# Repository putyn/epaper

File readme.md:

# epaper 
Adventure with epaper panel to create an epaper wifi connected photoframe.

Project is heavly based on [epdiy project](https://github.com/vroland/epdiy) but with a slightly different hardware, [epaper-breakout](epaper-breakout) is the first iteration of the project which will, hopefully, drive an ED060XC3 panel.

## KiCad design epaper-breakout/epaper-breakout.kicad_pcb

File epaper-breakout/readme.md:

`Project status: Work in progress`

## ink-frame rev 0.1

Breakout board for [TPS65185](https://www.ti.com/lit/ds/symlink/tps65185.pdf) which supplies the 5 voltages needed to drive e-ink panels, [BQ24075](https://www.ti.com/lit/ds/symlink/bq24075.pdf) 
battery charger and FPC connector for e-ink panel, should fit ED060XC3 panel.

## pcb render

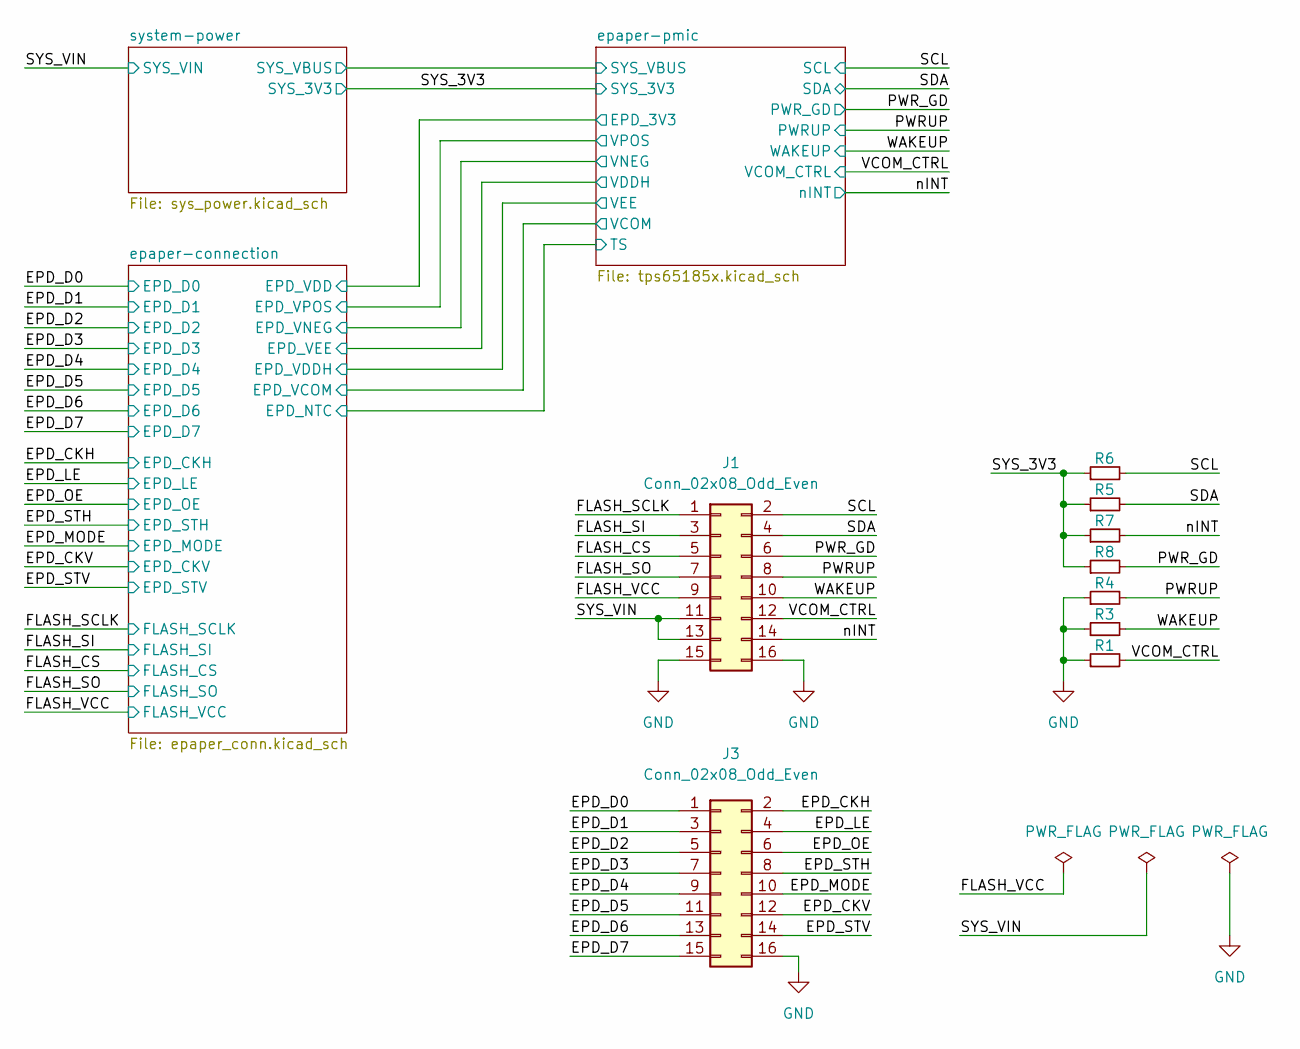
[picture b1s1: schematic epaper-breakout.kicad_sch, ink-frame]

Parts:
J1, J3: Conn_02x08_Odd_Even; PinHeader_2x08_P2.54mm_Vertical
R1, R3, R4, R7, R8: 100k; R_0603_1608Metric; LCSC C25803
R5, R6: 2k2; R_0603_1608Metric; LCSC C4190

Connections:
/EPD_CKH: J3.2; also elsewhere on the board
/EPD_CKV: J3.12; also elsewhere on the board
/EPD_D0: J3.1; also elsewhere on the board
/EPD_D1: J3.3; also elsewhere on the board
/EPD_D2: J3.5; also elsewhere on the board
/EPD_D3: J3.7; also elsewhere on the board
/EPD_D4: J3.9; also elsewhere on the board
/EPD_D5: J3.11; also elsewhere on the board
/EPD_D6: J3.13; also elsewhere on the board
/EPD_D7: J3.15; also elsewhere on the board
/EPD_LE: J3.4; also elsewhere on the board
/EPD_MODE: J3.10; also elsewhere on the board
/EPD_OE: J3.6; also elsewhere on the board
/EPD_STH: J3.8; also elsewhere on the board
/EPD_STV: J3.14; also elsewhere on the board
/FLASH_CS: J1.5; also elsewhere on the board
/FLASH_SCLK: J1.1; also elsewhere on the board
/FLASH_SI: J1.3; also elsewhere on the board
/FLASH_SO: J1.7; also elsewhere on the board
/FLASH_VCC: J1.9; also elsewhere on the board
/PWRUP: J1.8, R4.2; also elsewhere on the board
/PWR_GD: J1.6, R8.2; also elsewhere on the board
/SCL: J1.2, R6.2; also elsewhere on the board
/SDA: J1.4, R5.2; also elsewhere on the board
/SYS_3V3: R5.1, R6.1, R7.1, R8.1; also elsewhere on the board
/SYS_VIN: J1.11, J1.13; also elsewhere on the board
/VCOM_CTRL: J1.12, R1.2; also elsewhere on the board
/WAKEUP: J1.10, R3.2; also elsewhere on the board
/nINT: J1.14, R7.2; also elsewhere on the board
GND: J1.15, J1.16, J3.16, R1.1, R3.1, R4.1; also elsewhere on the board

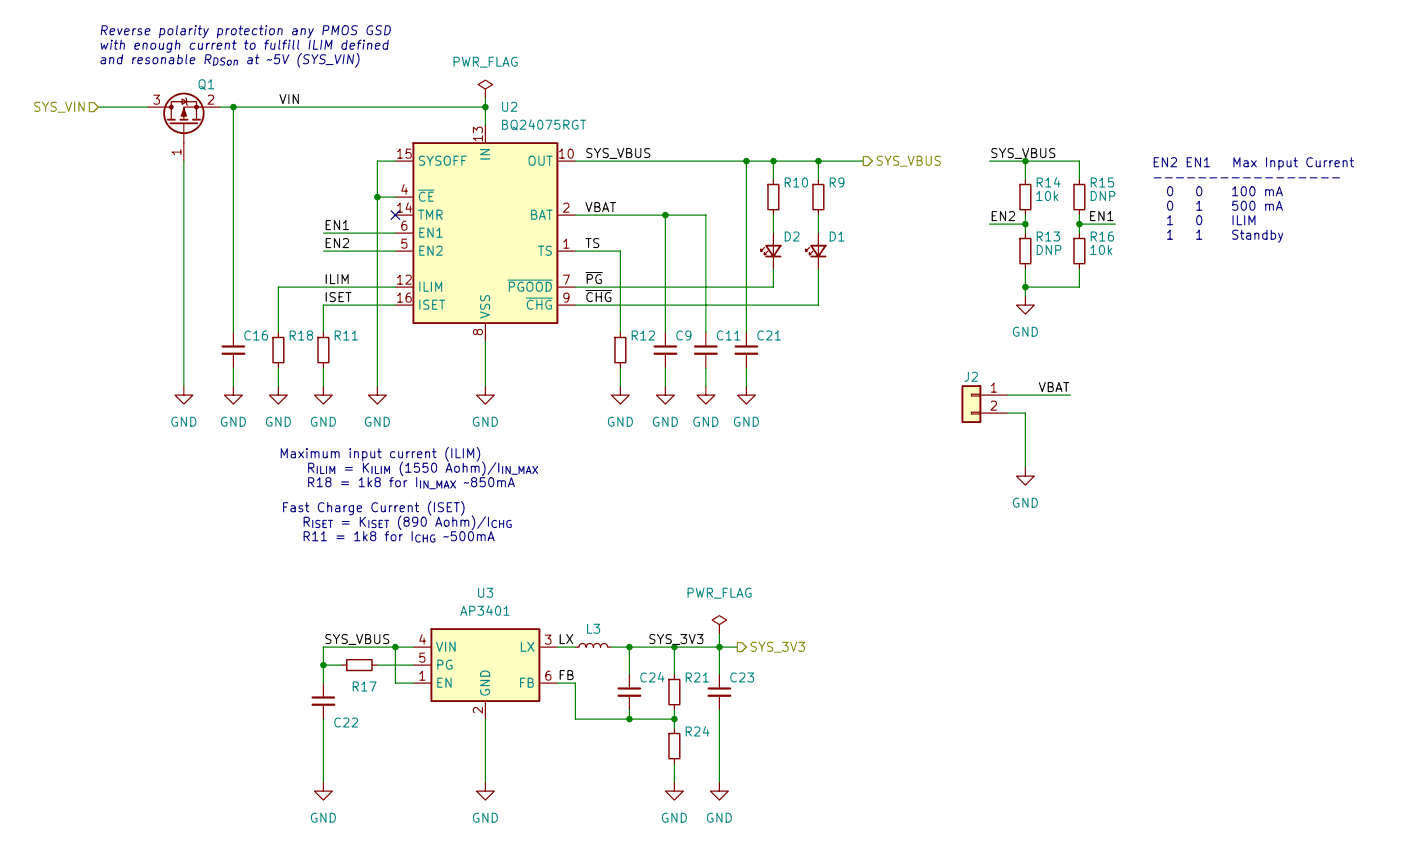
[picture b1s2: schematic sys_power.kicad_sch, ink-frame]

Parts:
C9, C16, C21, C22, C23: 10u;16V; C_0805_2012Metric; LCSC C17024
C11: 100n;25V; C_0603_1608Metric; LCSC C14663
C24: 22p; C_0603_1608Metric; LCSC C1653
D1, D2: RED; LED_0603_1608Metric; LCSC C965800
J2: Conn_01x02; JST_PH_S2B-PH-SM4-TB_1x02-1MP_P2.00mm_Horizontal; LCSC C47647
L3: 2u2; L_Taiyo-Yuden_NR-40xx; LCSC C98027
Q1: AO3401A; SOT-23; LCSC C15127
R9, R10: 2k2; R_0603_1608Metric; LCSC C4190
R11, R18: 1k8; R_0603_1608Metric; LCSC C4177
R12, R14, R16: 10k; R_0603_1608Metric; LCSC C25804
R13, R15: DNP; R_0603_1608Metric
R17, R24: 100k; R_0603_1608Metric; LCSC C25803
R21: 430k; R_0603_1608Metric; LCSC C25969
U2: BQ24075RGT; VQFN-16-1EP_3x3mm_P0.5mm_EP1.45x1.45mm_ThermalVias
U3: AP3401; TSOT-23-6

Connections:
/SYS_3V3: C23.1, C24.1, L3.2, R21.1; also elsewhere on the board
/SYS_VIN: Q1.3 (D); also elsewhere on the board
/epaper-pmic/SYS_VBUS: C21.1, C22.1, R9.1, R10.1, R14.1, R15.1, R17.1, U2.10 (OUT), U2.11 (OUT), U3.1 (EN), U3.4 (VIN); also elsewhere on the board
/system-power/EN1: R15.2, R16.1, U2.6 (EN1)
/system-power/EN2: R13.1, R14.2, U2.5 (EN2)
/system-power/FB: C24.2, R21.2, R24.1, U3.6 (FB)
/system-power/ILIM: R18.1, U2.12 (ILIM)
/system-power/ISET: R11.1, U2.16 (ISET)
/system-power/LX: L3.1, U3.3 (LX)
/system-power/TS: R12.1, U2.1 (TS)
/system-power/VBAT: C9.1, C11.1, J2.1, U2.2 (BAT), U2.3 (BAT)
/system-power/VIN: C16.1, Q1.2 (S), U2.13 (IN)
/system-power/~CHG: D1.1 (K), U2.9 (~CHG)
/system-power/~PG: D2.1 (K), U2.7 (~PGOOD)
GND: C9.2, C11.2, C16.2, C21.2, C22.2, C23.2, J2.2, Q1.1 (G), R11.2, R12.2, R13.2, R16.2, R18.2, R24.2, U2.4 (~CE), U2.8 (VSS), U2.15 (SYSOFF), U2.17 (VSS), U3.2 (GND); also elsewhere on the board
unnamed: D1.2 (A), R9.2
unnamed: D2.2 (A), R10.2
unnamed: R17.2, U3.5 (PG)

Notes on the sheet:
Maximum input current (ILIM) R_{ILIM} = K_{ILIM} (1550 Aohm)/I_{IN_MAX} R18 = 1k8 for I_{IN_MAX} ~850mA
Fast Charge Current (ISET) R_{ISET} = K_{ISET} (890 Aohm)/I_{CHG} R11 = 1k8 for I_{CHG} ~500mA
EN2 EN1 Max Input Current ----------------- 0 0 100 mA 0 1 500 mA 1 0 ILIM 1 1 Standby
Reverse polarity protection any PMOS GSD with enough current to fulfill ILIM defined and resonable R_{DSon} at ~5V (SYS_VIN)

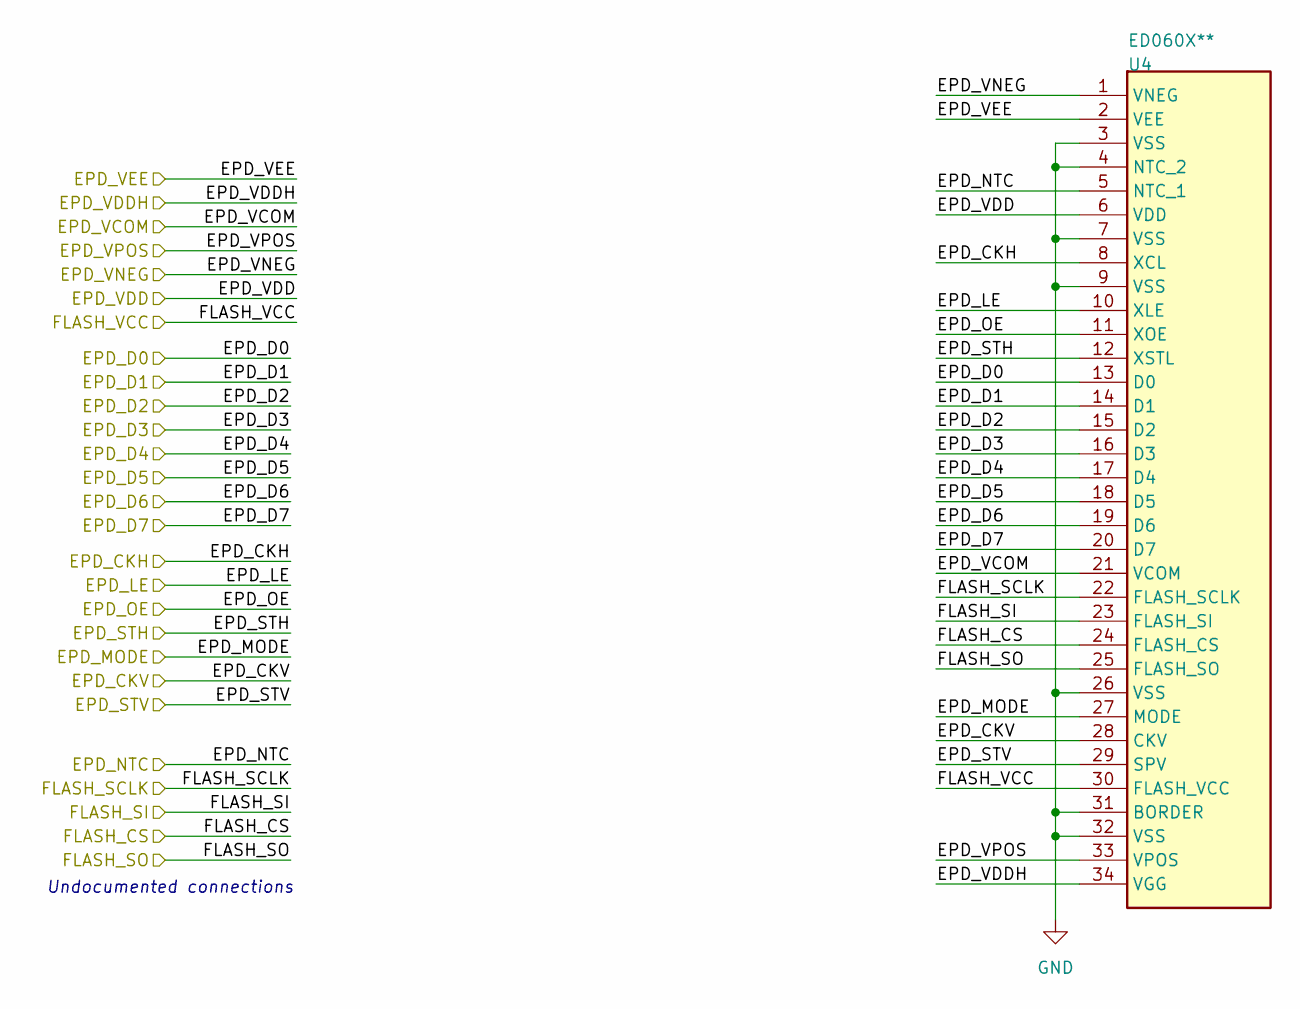
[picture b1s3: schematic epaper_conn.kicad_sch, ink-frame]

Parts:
U4: ED060X**; THD_THD0515-34CL-SN; LCSC C283154

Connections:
/EPD_CKH: U4.8 (XCL); also elsewhere on the board
/EPD_CKV: U4.28 (CKV); also elsewhere on the board
/EPD_D0: U4.13 (D0); also elsewhere on the board
/EPD_D1: U4.14 (D1); also elsewhere on the board
/EPD_D2: U4.15 (D2); also elsewhere on the board
/EPD_D3: U4.16 (D3); also elsewhere on the board
/EPD_D4: U4.17 (D4); also elsewhere on the board
/EPD_D5: U4.18 (D5); also elsewhere on the board
/EPD_D6: U4.19 (D6); also elsewhere on the board
/EPD_D7: U4.20 (D7); also elsewhere on the board
/EPD_LE: U4.10 (XLE); also elsewhere on the board
/EPD_MODE: U4.27 (MODE); also elsewhere on the board
/EPD_OE: U4.11 (XOE); also elsewhere on the board
/EPD_STH: U4.12 (XSTL); also elsewhere on the board
/EPD_STV: U4.29 (SPV); also elsewhere on the board
/FLASH_CS: U4.24 (FLASH_CS); also elsewhere on the board
/FLASH_SCLK: U4.22 (FLASH_SCLK); also elsewhere on the board
/FLASH_SI: U4.23 (FLASH_SI); also elsewhere on the board
/FLASH_SO: U4.25 (FLASH_SO); also elsewhere on the board
/FLASH_VCC: U4.30 (FLASH_VCC); also elsewhere on the board
/epaper-connection/EPD_NTC: U4.5 (NTC_1); also elsewhere on the board
/epaper-connection/EPD_VCOM: U4.21 (VCOM); also elsewhere on the board
/epaper-connection/EPD_VDD: U4.6 (VDD); also elsewhere on the board
/epaper-connection/EPD_VDDH: U4.34 (VGG); also elsewhere on the board
/epaper-connection/EPD_VEE: U4.2 (VEE); also elsewhere on the board
/epaper-connection/EPD_VNEG: U4.1 (VNEG); also elsewhere on the board
/epaper-connection/EPD_VPOS: U4.33 (VPOS); also elsewhere on the board
GND: U4.3 (VSS), U4.4 (NTC_2), U4.7 (VSS), U4.9 (VSS), U4.26 (VSS), U4.31 (BORDER), U4.32 (VSS); also elsewhere on the board

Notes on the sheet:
Undocumented connections

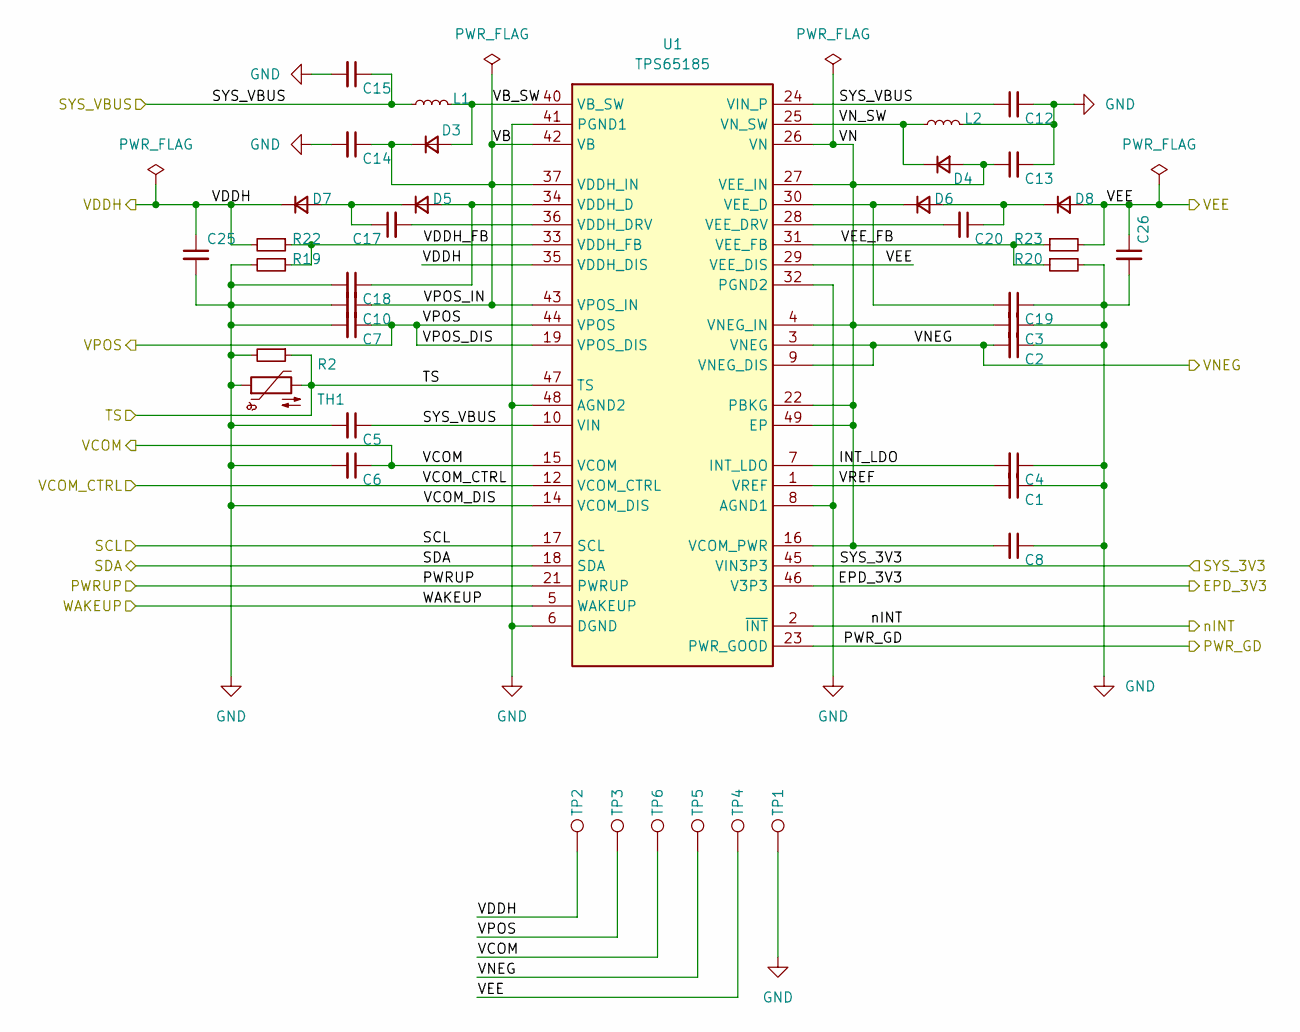
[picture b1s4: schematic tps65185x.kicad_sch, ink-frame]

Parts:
C1, C4, C6: 4u7;6V3; C_0603_1608Metric; LCSC C8032
C2, C3, C7, C8, C10, C13, C14: 4u7;25V; C_0805_2012Metric; LCSC C1779
C5, C12, C15: 10u;16V; C_0805_2012Metric; LCSC C17024
C17, C20: 10n;25V; C_0603_1608Metric; LCSC C1589
C18, C19: 100n;25V; C_0603_1608Metric; LCSC C14663
C25, C26: 4u7;50V; C_0805_2012Metric; LCSC C98192
D3, D4, D5, D6, D7, D8: 1N5819WS; D_SOD-323; LCSC C191023
L1: 2u2; L_Taiyo-Yuden_NR-40xx; LCSC C98027
L2: 4u7; L_Taiyo-Yuden_NR-40xx; LCSC C86081
R2: 43k; R_0603_1608Metric; LCSC C23172
R19: 47k5; R_0603_1608Metric; LCSC C25896
R20: 52k3; R_0603_1608Metric; LCSC C23198
R22, R23: 1M; R_0603_1608Metric; LCSC C22935
TH1: 10k; R_0603_1608Metric; LCSC C13564
TP1, TP2, TP3, TP4, TP5, TP6: TestPoint; TestPoint_Pad_D1.5mm
U1: TPS65185; VQFN-48-1EP_7x7mm_P0.5mm_EP4.1x4.1mm_ThermalVias

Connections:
/PWRUP: U1.21 (PWRUP); also elsewhere on the board
/PWR_GD: U1.23 (PWR_GOOD); also elsewhere on the board
/SCL: U1.17 (SCL); also elsewhere on the board
/SDA: U1.18 (SDA); also elsewhere on the board
/SYS_3V3: U1.45 (VIN3P3); also elsewhere on the board
/VCOM_CTRL: U1.12 (VCOM_CTRL); also elsewhere on the board
/WAKEUP: U1.5 (WAKEUP); also elsewhere on the board
/epaper-connection/EPD_NTC: R2.1, TH1.2, U1.47 (TS); also elsewhere on the board
/epaper-connection/EPD_VCOM: C6.1, TP6.1, U1.15 (VCOM); also elsewhere on the board
/epaper-connection/EPD_VDD: U1.46 (V3P3); also elsewhere on the board
/epaper-connection/EPD_VDDH: C26.1, D8.2 (A), R23.2, TP4.1, U1.29 (VEE_DIS); also elsewhere on the board
/epaper-connection/EPD_VEE: C25.1, D7.1 (K), R22.2, TP2.1, U1.35 (VDDH_DIS); also elsewhere on the board
/epaper-connection/EPD_VNEG: C2.2, TP5.1, U1.3 (VNEG), U1.9 (VNEG_DIS); also elsewhere on the board
/epaper-connection/EPD_VPOS: C7.1, TP3.1, U1.19 (VPOS_DIS), U1.44 (VPOS); also elsewhere on the board
/epaper-pmic/INT_LDO: C4.2, U1.7 (INT_LDO)
/epaper-pmic/SYS_VBUS: C5.1, C12.1, C15.1, L1.1, U1.10 (VIN), U1.24 (VIN_P); also elsewhere on the board
/epaper-pmic/VDDH_FB: R19.1, R22.1, U1.33 (VDDH_FB)
/epaper-pmic/VEE_FB: R20.1, R23.1, U1.31 (VEE_FB)
/epaper-pmic/VN: C3.2, C8.2, C13.1, D4.2 (A), U1.4 (VNEG_IN), U1.16 (VCOM_PWR), U1.22 (PBKG), U1.26 (VN), U1.27 (VEE_IN), U1.49 (EP)
/epaper-pmic/VN_SW: D4.1 (K), L2.2, U1.25 (VN_SW)
/epaper-pmic/VREF: C1.2, U1.1 (VREF)
/nINT: U1.2 (~INT); also elsewhere on the board
GND: C1.1, C2.1, C3.1, C4.1, C5.2, C6.2, C7.2, C8.1, C10.2, C12.2, C13.2, C14.2, C15.2, C18.2, C19.1, C25.2, C26.2, L2.1, R2.2, R19.2, R20.2, TH1.1, TP1.1, U1.6 (DGND), U1.8 (AGND1), U1.14 (VCOM_DIS), U1.32 (PGND2), U1.41 (PGND1), U1.48 (AGND2); also elsewhere on the board
unnamed: C17.1, D5.1 (K), D7.2 (A)
unnamed: C17.2, U1.36 (VDDH_DRV)
unnamed: C18.1, D5.2 (A), U1.34 (VDDH_D)
unnamed 58: C19.2, D6.1 (K), U1.30 (VEE_D); also elsewhere on the board
unnamed 59: C20.1, D6.2 (A), D8.1 (K); also elsewhere on the board
unnamed: C20.2, U1.28 (VEE_DRV)

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
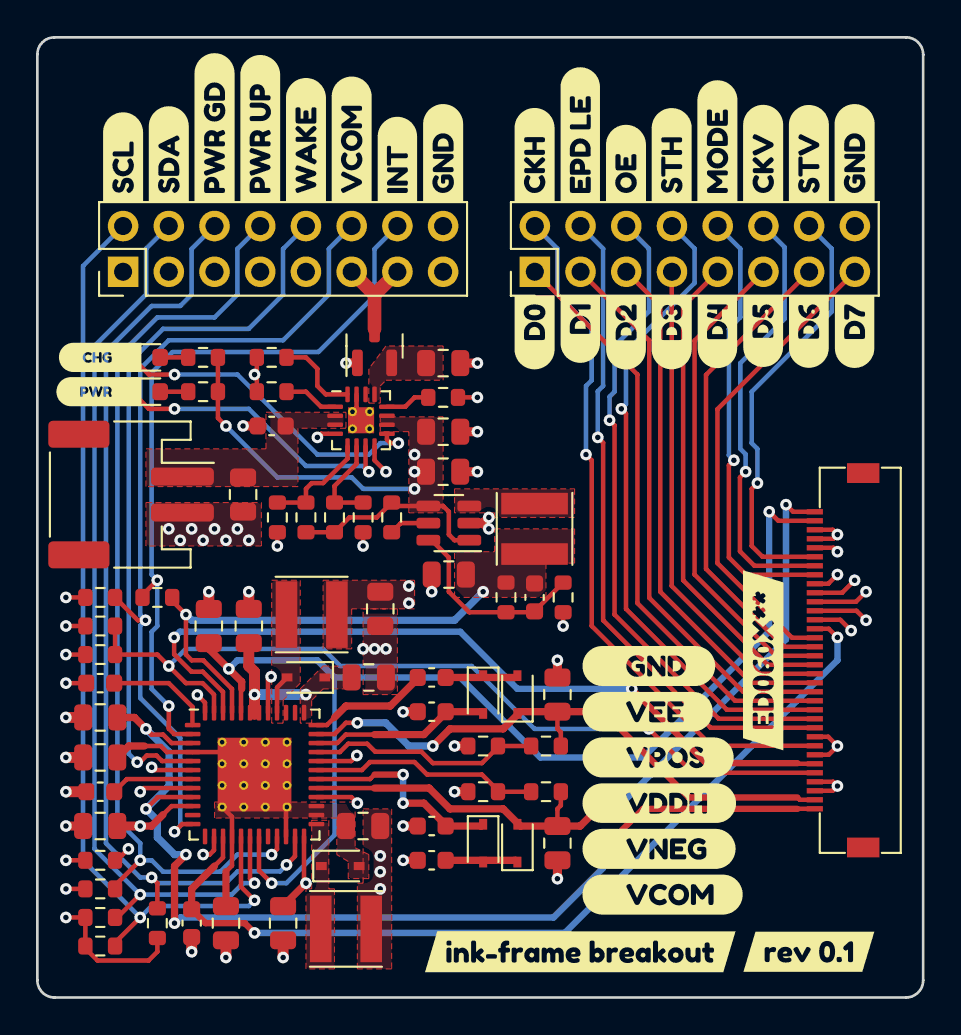
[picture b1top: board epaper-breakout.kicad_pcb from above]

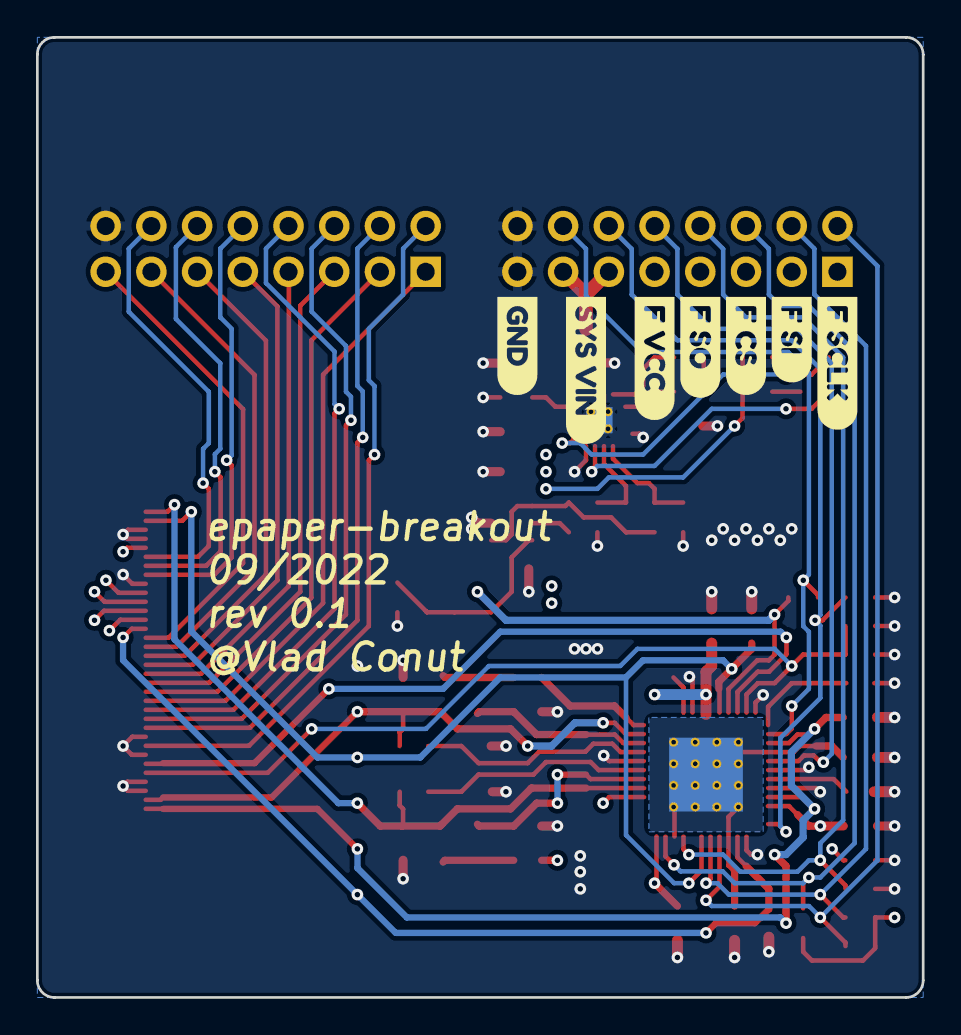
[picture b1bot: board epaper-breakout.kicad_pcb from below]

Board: 4 copper layers, 49.2 x 53.3 mm, 118 parts (7 on the bottom side), 66 nets.

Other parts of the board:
kibuzzard-1: G***; kibuzzard-63060977
kibuzzard-2: G***; kibuzzard-6306091E
kibuzzard-3: G***; kibuzzard-6304CD62
kibuzzard-4: G***; kibuzzard-6304CD58
kibuzzard-5: G***; kibuzzard-6304CD7C
kibuzzard-6: G***; kibuzzard-6304CD98
kibuzzard-7: G***; kibuzzard-6304CDA2
kibuzzard-8: G***; kibuzzard-6304CE57
kibuzzard-9: G***; kibuzzard-6304CE9C
kibuzzard-10, kibuzzard-34, kibuzzard-34#2: G***; kibuzzard-6304CEA6
kibuzzard-11: G***; kibuzzard-6304CAAC
kibuzzard-12: G***; kibuzzard-6304CBD9
kibuzzard-13: G***; kibuzzard-6304CA26
kibuzzard-14: G***; kibuzzard-6304CBCE
kibuzzard-15: G***; kibuzzard-6307DF07
kibuzzard-16: G***; kibuzzard-6304CA4F
kibuzzard-17: G***; kibuzzard-6304CBC7
kibuzzard-18: G***; kibuzzard-6305306A
kibuzzard-19: G***; kibuzzard-63052A6A
kibuzzard-20: G***; kibuzzard-63052A59
kibuzzard-21: G***; kibuzzard-63052A0A
kibuzzard-22: G***; kibuzzard-630529E3
kibuzzard-23: G***; kibuzzard-63052909
kibuzzard-24: G***; kibuzzard-6304CA73
kibuzzard-25: G***; kibuzzard-6304CBC0
kibuzzard-26: G***; kibuzzard-6304CA80
kibuzzard-27: G***; kibuzzard-6304CBB8
kibuzzard-28: G***; kibuzzard-6304CA8E
kibuzzard-29: G***; kibuzzard-6304CBAE
kibuzzard-30: G***; kibuzzard-6304C9DD
kibuzzard-31: G***; kibuzzard-6304CA9B
kibuzzard-32: G***; kibuzzard-6304CBA2
kibuzzard-33: G***; kibuzzard-63108B63
kibuzzard-35: G***; kibuzzard-6304CB97
kibuzzard-631C7B6B: G***; kibuzzard-631C7B6B
kibuzzard-631C7BA9: G***; kibuzzard-631C7BA9
kibuzzard-631C7BBA: G***; kibuzzard-631C7BBA
kibuzzard-631C7BCA: G***; kibuzzard-631C7BCA
kibuzzard-631C7BDB: G***; kibuzzard-631C7BDB
kibuzzard-631C7BE9: G***; kibuzzard-631C7BE9
locked: B5819WS; D_SOD-323
locked#2: B5819WS; D_SOD-323

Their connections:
/epaper-connection/EPD_VDDH: locked#2.2 (A); also elsewhere on the board
unnamed 58: locked.1 (K); also elsewhere on the board
unnamed 59: locked.2 (A), locked#2.1 (K); also elsewhere on the board

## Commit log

2023-01-09 various display specs found around the internet and first hardware iteration
2023-01-09 added readme
2023-01-10 playing with github actions
2023-01-20 schematic and PCB front side render
